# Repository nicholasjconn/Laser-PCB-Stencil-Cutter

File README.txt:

This repository is for the PCB laser stencil cutter project posted on Hardware Breakout.

http://hardwarebreakout.com/2013/03/diy-laser-cutter-for-pcb-stencils

The folder "NJC Laser Sprinter Firmware" is based off of the RAMPS sprinter firmware, built for the RepRap. The eagle_stencil.cam is the CAM process which creates gerber files for each stencil for a given board layout. The GerberToGCODE python file will convert a gerber file created in Eagle CAD to gcode readable by the RAMPS firmware. Finally, an example stencil is provided in the Stencils folder.

Feel free to modify all of these as needed, just please give credit where credit is due.

Nicholas J. Conn
Hardware Breakout
NJC@hardwarebreakout.com
http://hardwarebreakout.com

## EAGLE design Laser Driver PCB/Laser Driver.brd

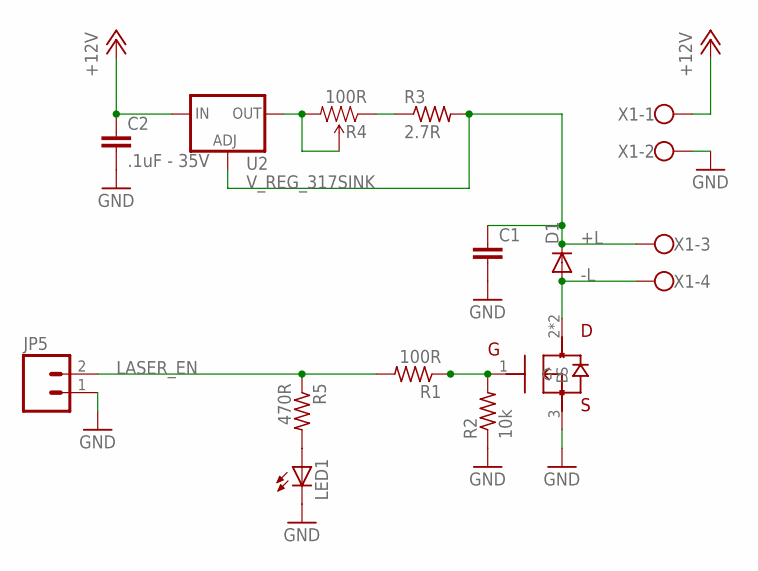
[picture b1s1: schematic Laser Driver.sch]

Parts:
C1: C-EUC0805; C0805
C2: .1uF - 35V; C1206
D1: DIODEPTH; DIODE-1N4001
JP5: M02PTH; 1X02
LED1: LEDCHIPLED_0805; CHIPLED_0805
R1: 100R; R0805
R2: 10k; R0805
R3: 2.7R; 0411/12
R4: 100R; 3362U-2
R5: 470R; R0805
U2: V_REG_317SINK; TO220-ADJ
U$2: MOSFET; SOT223
X1: W237-4

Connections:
+12V: C2.1, U2.IN, X1.1
+L: C1.1, D1.C, R3.2, U2.ADJ, X1.3
-L: D1.A, U$2.2 (D), U$2.4 (D), X1.4
GND: C1.2, C2.2, JP5.1, LED1.C, R2.1, U$2.3 (S), X1.2
LASER_EN: JP5.2, R1.2, R5.1
LED_ON: R1.1, R2.2, U$2.1 (G)
unnamed: LED1.A, R5.2
unnamed: R4.2 (WIPER), R4.3 (CW), U2.OUT
unnamed: R3.1, R4.1 (CCW)

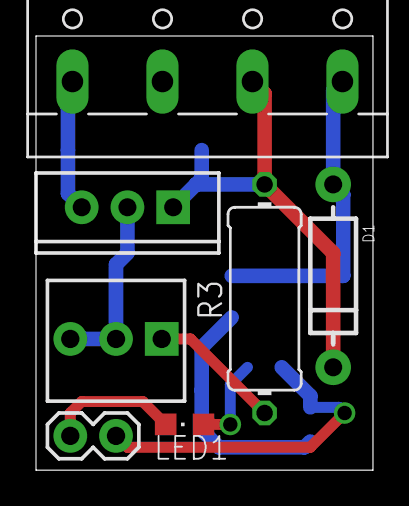
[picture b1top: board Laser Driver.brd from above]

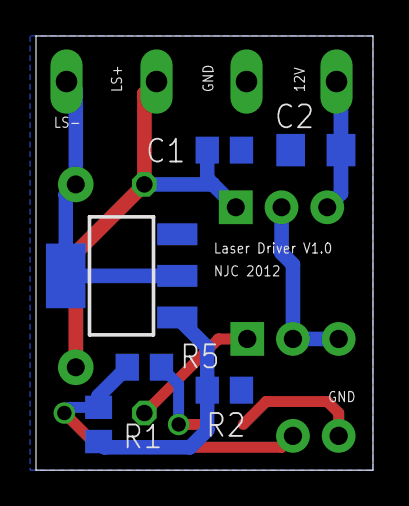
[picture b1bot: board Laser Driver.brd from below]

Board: 2 copper layers, 18.7 x 24.1 mm, 13 parts (6 on the bottom side), 9 nets.

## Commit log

2013-03-30 Initial commit before blog post.
2013-03-30 Added Eagle CAD files for the laser driver board.

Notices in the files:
parts and their libraries:
SparkFun: Licensing: CC v3.0 Share-Alike You are welcome to use this library for commercial purposes.
